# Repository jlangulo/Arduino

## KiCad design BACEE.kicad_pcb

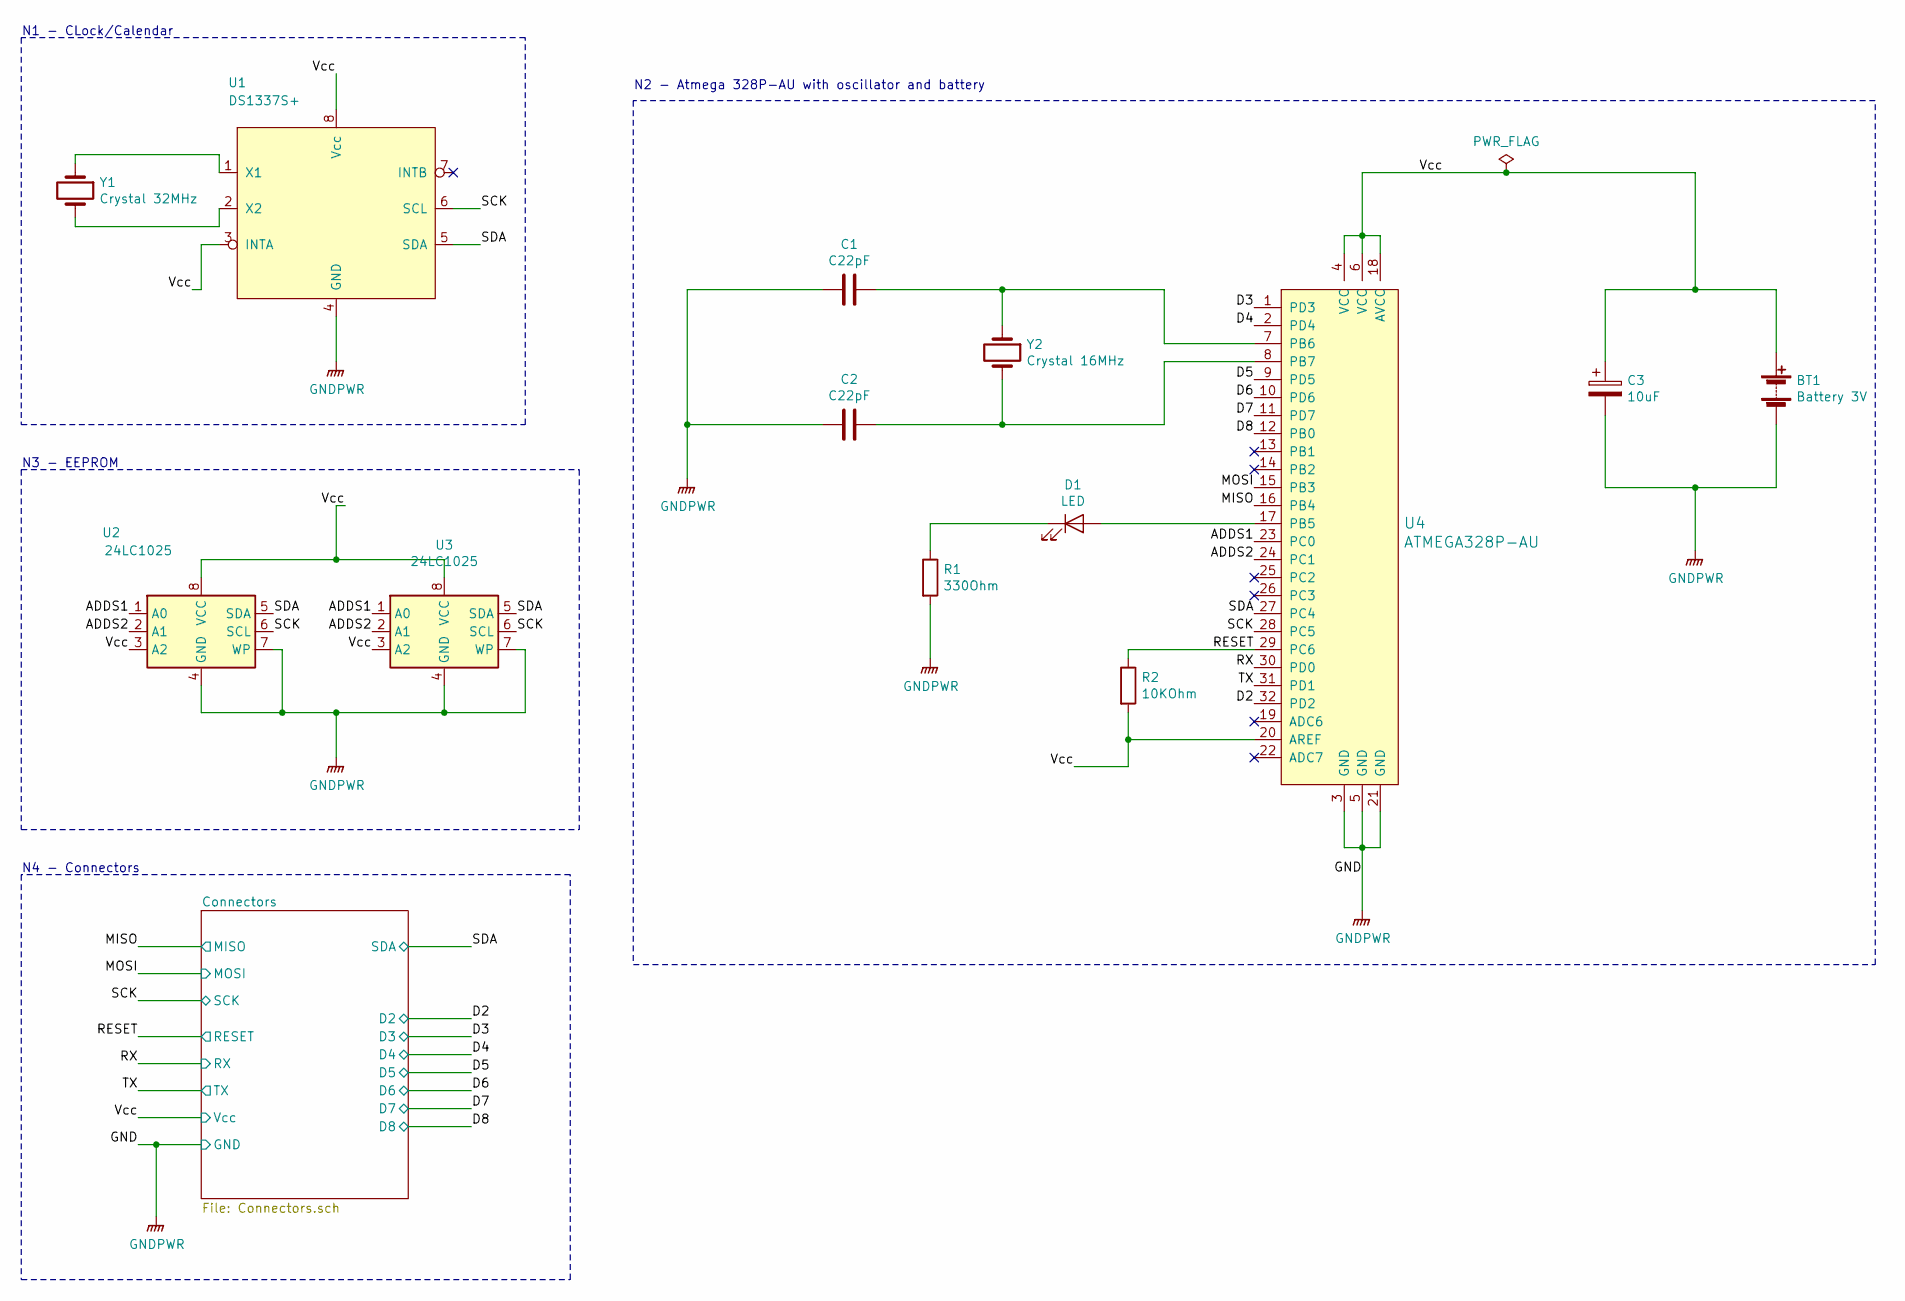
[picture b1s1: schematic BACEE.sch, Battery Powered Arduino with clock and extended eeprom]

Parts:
BT1: Battery 3V; PinHeader_1x02_P2.54mm_Vertical
C1, C2: C22pF; C_0805_2012Metric_Pad1.15x1.40mm_HandSolder
C3: 10uF; C_0805_2012Metric_Pad1.15x1.40mm_HandSolder
D1: LED; LED_0805_2012Metric_Pad1.15x1.40mm_HandSolder
R1: 330Ohm; R_0805_2012Metric_Pad1.15x1.40mm_HandSolder
R2: 10KOhm; R_0805_2012Metric_Pad1.15x1.40mm_HandSolder
U1: DS1337S+; SOIJ-8_5.3x5.3mm_P1.27mm
U2: 24LC1025; SOIJ-8_5.3x5.3mm_P1.27mm
U3: 24LC1025; SO-8_5.3x6.2mm_P1.27mm
U4: ATMEGA328P-AU; TQFP-32_7x7mm; MPN ATMEGA328P-AU; Digi-Key_PN ATMEGA328P-AU-ND
Y1: Crystal 32MHz; Crystal_SMD_MicroCrystal_CC7V-T1A-2Pin_3.2x1.5mm
Y2: Crystal 16MHz; Crystal_SMD_5032-2Pin_5.0x3.2mm_HandSoldering

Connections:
/ADDS1: U2.1 (A0), U3.1 (A0), U4.23 (PC0)
/ADDS2: U2.2 (A1), U3.2 (A1), U4.24 (PC1)
/D2: U4.32 (PD2); also elsewhere on the board
/D3: U4.1 (PD3); also elsewhere on the board
/D4: U4.2 (PD4); also elsewhere on the board
/D5: U4.9 (PD5); also elsewhere on the board
/D6: U4.10 (PD6); also elsewhere on the board
/D7: U4.11 (PD7); also elsewhere on the board
/D8: U4.12 (PB0); also elsewhere on the board
/MISO: U4.16 (PB4); also elsewhere on the board
/MOSI: U4.15 (PB3); also elsewhere on the board
/RESET: R2.1, U4.29 (PC6); also elsewhere on the board
/RX: U4.30 (PD0); also elsewhere on the board
/SCK: U1.6 (SCL), U2.6 (SCL), U3.6 (SCL), U4.28 (PC5); also elsewhere on the board
/SDA: U1.5 (SDA), U2.5 (SDA), U3.5 (SDA), U4.27 (PC4); also elsewhere on the board
/TX: U4.31 (PD1); also elsewhere on the board
/Vcc: BT1.1 (+), C3.1, R2.2, U1.3 (INTA), U1.8 (Vcc), U2.3 (A2), U2.8 (VCC), U3.3 (A2), U3.8 (VCC), U4.4 (VCC), U4.6 (VCC), U4.18 (AVCC), U4.20 (AREF); also elsewhere on the board
GNDPWR: BT1.2 (-), C1.2, C2.2, C3.2, R1.2, U1.4 (GND), U2.4 (GND), U2.7 (WP), U3.4 (GND), U3.7 (WP), U4.3 (GND), U4.5 (GND), U4.21 (GND); also elsewhere on the board
unnamed: C1.1, U4.7 (PB6), Y2.1
unnamed: C2.1, U4.8 (PB7), Y2.2
unnamed: D1.1 (K), R1.1
unnamed: D1.2 (A), U4.17 (PB5)
unnamed: U1.1 (X1), Y1.1
unnamed: U1.2 (X2), Y1.2

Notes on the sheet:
N1 - CLock/Calendar
N2 - Atmega 328P-AU with oscillator and battery
N3 - EEPROM
N4 - Connectors

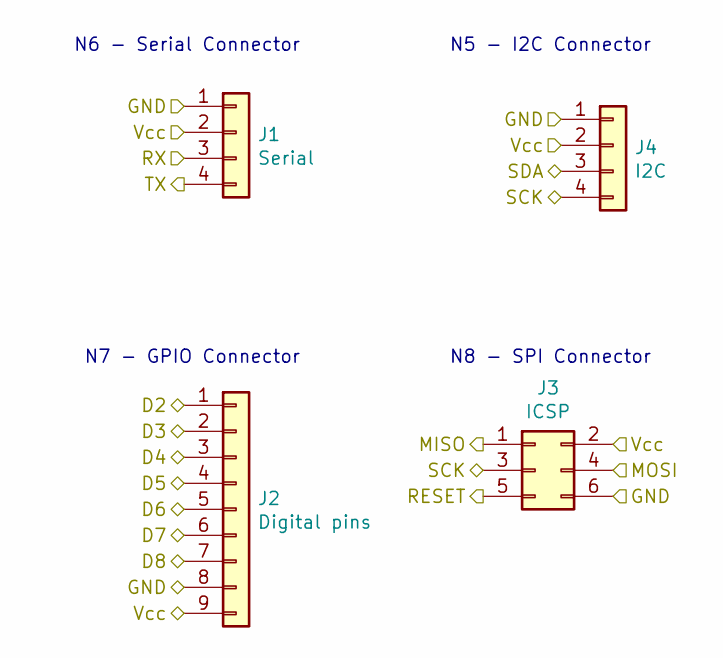
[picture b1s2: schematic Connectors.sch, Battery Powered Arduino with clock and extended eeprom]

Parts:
J1: Serial; PinSocket_1x04_P2.54mm_Vertical
J2: Digital pins; PinSocket_1x09_P2.54mm_Vertical
J3: ICSP; PinSocket_2x03_P2.54mm_Vertical
J4: I2C; PinSocket_1x04_P2.54mm_Vertical

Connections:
/D2: J2.1; also elsewhere on the board
/D3: J2.2; also elsewhere on the board
/D4: J2.3; also elsewhere on the board
/D5: J2.4; also elsewhere on the board
/D6: J2.5; also elsewhere on the board
/D7: J2.6; also elsewhere on the board
/D8: J2.7; also elsewhere on the board
/MISO: J3.1; also elsewhere on the board
/MOSI: J3.4; also elsewhere on the board
/RESET: J3.5; also elsewhere on the board
/RX: J1.3; also elsewhere on the board
/SCK: J3.3, J4.4; also elsewhere on the board
/SDA: J4.3; also elsewhere on the board
/TX: J1.4; also elsewhere on the board
/Vcc: J1.2, J2.9, J3.2, J4.2; also elsewhere on the board
GNDPWR: J1.1, J2.8, J3.6, J4.1; also elsewhere on the board

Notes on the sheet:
N6 - Serial Connector
N5 - I2C Connector
N7 - GPIO Connector
N8 - SPI Connector

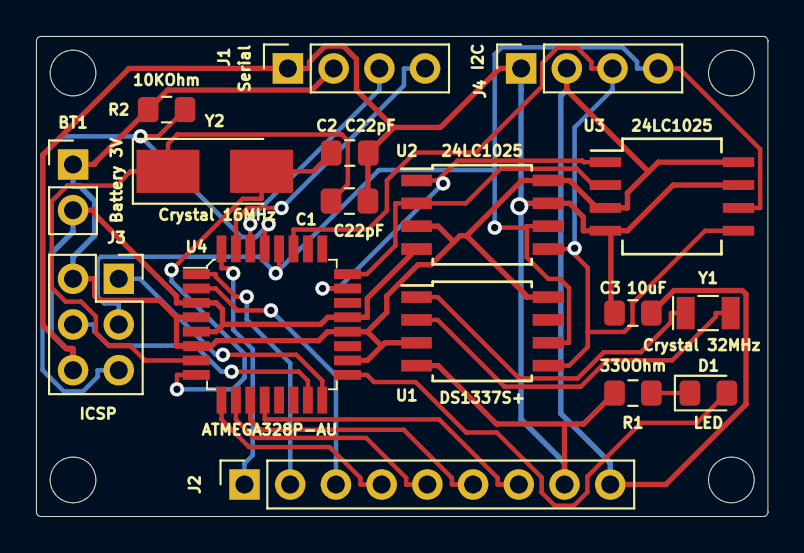
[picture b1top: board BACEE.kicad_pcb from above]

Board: 2 copper layers, 40.6 x 26.7 mm, 17 parts (0 on the bottom side), 24 nets.

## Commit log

2020-05-17 Added KiCAD files
2020-05-17 Setup the title block in schematic
2020-05-17 Create new shild sheet, added roject symbols
2020-05-17 Added symbol for Atmega328p-au
2020-05-17 Added clock IC Custom symbol
2020-05-17 Added crystals
2020-05-17 Arranged Symbols
2020-05-17 Annotated.
2020-05-17 Addded footprints
2020-05-17 Completed wiring in connector sheet
2020-05-17 Completed wiring in root sheet
2020-05-17 Corrected the Atmega unconnected pins
2020-05-17 Added functional block descriptions
2020-05-17 Created netlist file
2020-05-17 Started work in PCBnew
2020-05-17 Set design rules.
2020-05-17 Placement complete
2020-05-17 Compleated Outlines and mounting holes
2020-05-17 Compleated Outlines and mounting holes, corrected
2020-05-17 Autorouting completed
2020-05-17 Created copper field ares
2020-05-17 Added and resizwed Silk screen
